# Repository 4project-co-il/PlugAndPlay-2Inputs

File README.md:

# PlugAndPlay: Input module with 2 screw terminals
This is the repository with the files for PlugAndPlay input module with 2 screw terminals

That module has 2 screw terminals, connected to the 2 interrupt lines of the PnP connector and configured to provide interrupt on any change of each input.

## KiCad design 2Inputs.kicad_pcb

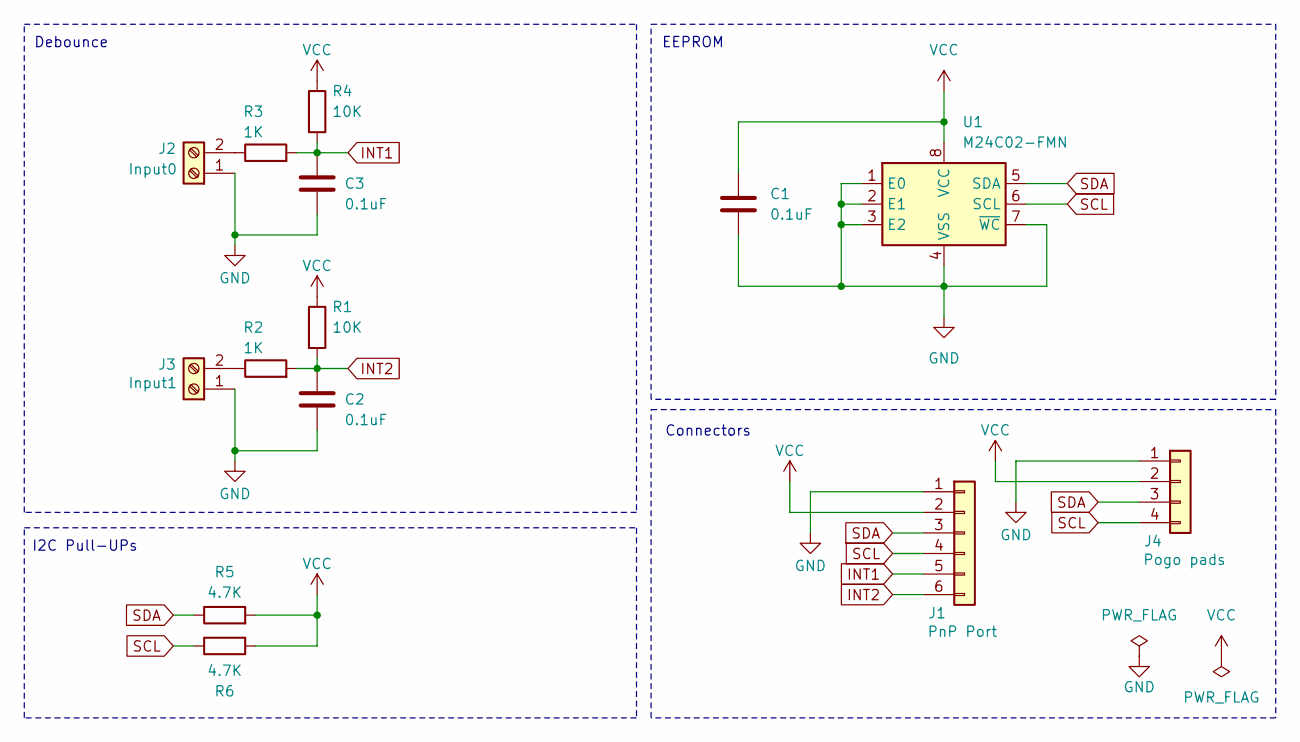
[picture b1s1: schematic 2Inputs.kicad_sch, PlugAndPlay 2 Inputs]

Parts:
C1, C2, C3: 0.1uF; C_0603_1608Metric; MPN C14663
J1: JST_SH_SM06B-SRSS-TB_1x06-1MP_P1.00mm_Horizontal; MPN C7430448
J2: Input0; TerminalBlock_4Ucon_1x02_P3.50mm_Horizontal
J3: Input1; TerminalBlock_4Ucon_1x02_P3.50mm_Horizontal
J4: Conn_01x04; PogoPinsPads_1x04_P2.5mm
R1, R4: 10K; R_0603_1608Metric; MPN C25804
R2, R3: 1K; R_0603_1608Metric; MPN C21190
R5, R6: 4.7K; R_0603_1608Metric; MPN C4190
U1: M24C02-FMN; SOIC-8_3.9x4.9mm_P1.27mm; MPN C114502

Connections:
GND: C1.2, C2.2, C3.2, J1.1, J2.1, J3.1, J4.1, U1.1 (E0), U1.2 (E1), U1.3 (E2), U1.4 (VSS), U1.7 (~WC)
INT1: C3.1, J1.5, R3.2, R4.2
INT2: C2.1, J1.6, R1.2, R2.2
unnamed: J2.2, R3.1
unnamed: J3.2, R2.1
SCL: J1.4, J4.4, R6.1, U1.6 (SCL)
SDA: J1.3, J4.3, R5.1, U1.5 (SDA)
VCC: C1.1, J1.2, J4.2, R1.1, R4.1, R5.2, R6.2, U1.8 (VCC)

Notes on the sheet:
EEPROM
Connectors
I2C Pull-UPs
Debounce

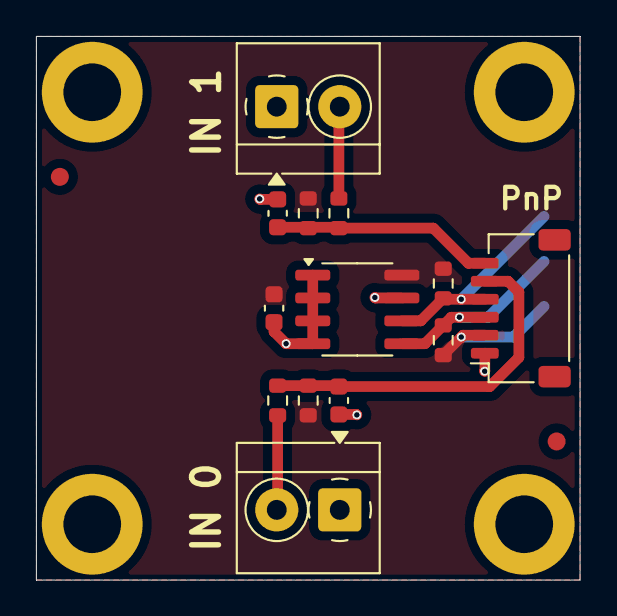
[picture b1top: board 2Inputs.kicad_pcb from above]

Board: 2 copper layers, 30.2 x 30.2 mm, 14 parts (1 on the bottom side), 8 nets.

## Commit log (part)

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2025-10-23 Change screw terminals to 3.5mm version
2025-10-30 Hide bottom pads connector silk printouts
2026-01-12 Invert IN0 and IN1 labels
